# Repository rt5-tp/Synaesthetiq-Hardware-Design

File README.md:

# SynaesthetiQ Hardware

SynaesthetiQ's hardware centre's around a pair of flexible LED Matrices which have been wrapped around a 3D printed core, palced on top of this core is a 30W RGB COB LED.

## AuxBoard

SynaesthetiQ has an Auxillary Board which provides power to both of the matrices, the big led, Raspberry Pi 4B and a fan for cooling. This board is detailed in the [AuxBoard KiCAD project](./AuxBoard/). This board distributes power provided by an ATX power supply while also providing Back Powering protection from the RPI and polyfuse protection to each of the four areas of supply on the board. AuxBoard provides levelshifting from the 3.3v of the RPI's logic to the 5v of the matrices and the big LED.

### Schematic

### PCB Layout

### Final PCB's
The most recent PCB for the project.

Below is two of the eventual three PCBs made for the project.

## PMOS Switch

Exists to test the functionality of the PMOS Switch circuit being used.

## ZVD Sim

Is a KiCAD project which simulates the Back powering protection built into the SynaesthetiQ AuxBoard.

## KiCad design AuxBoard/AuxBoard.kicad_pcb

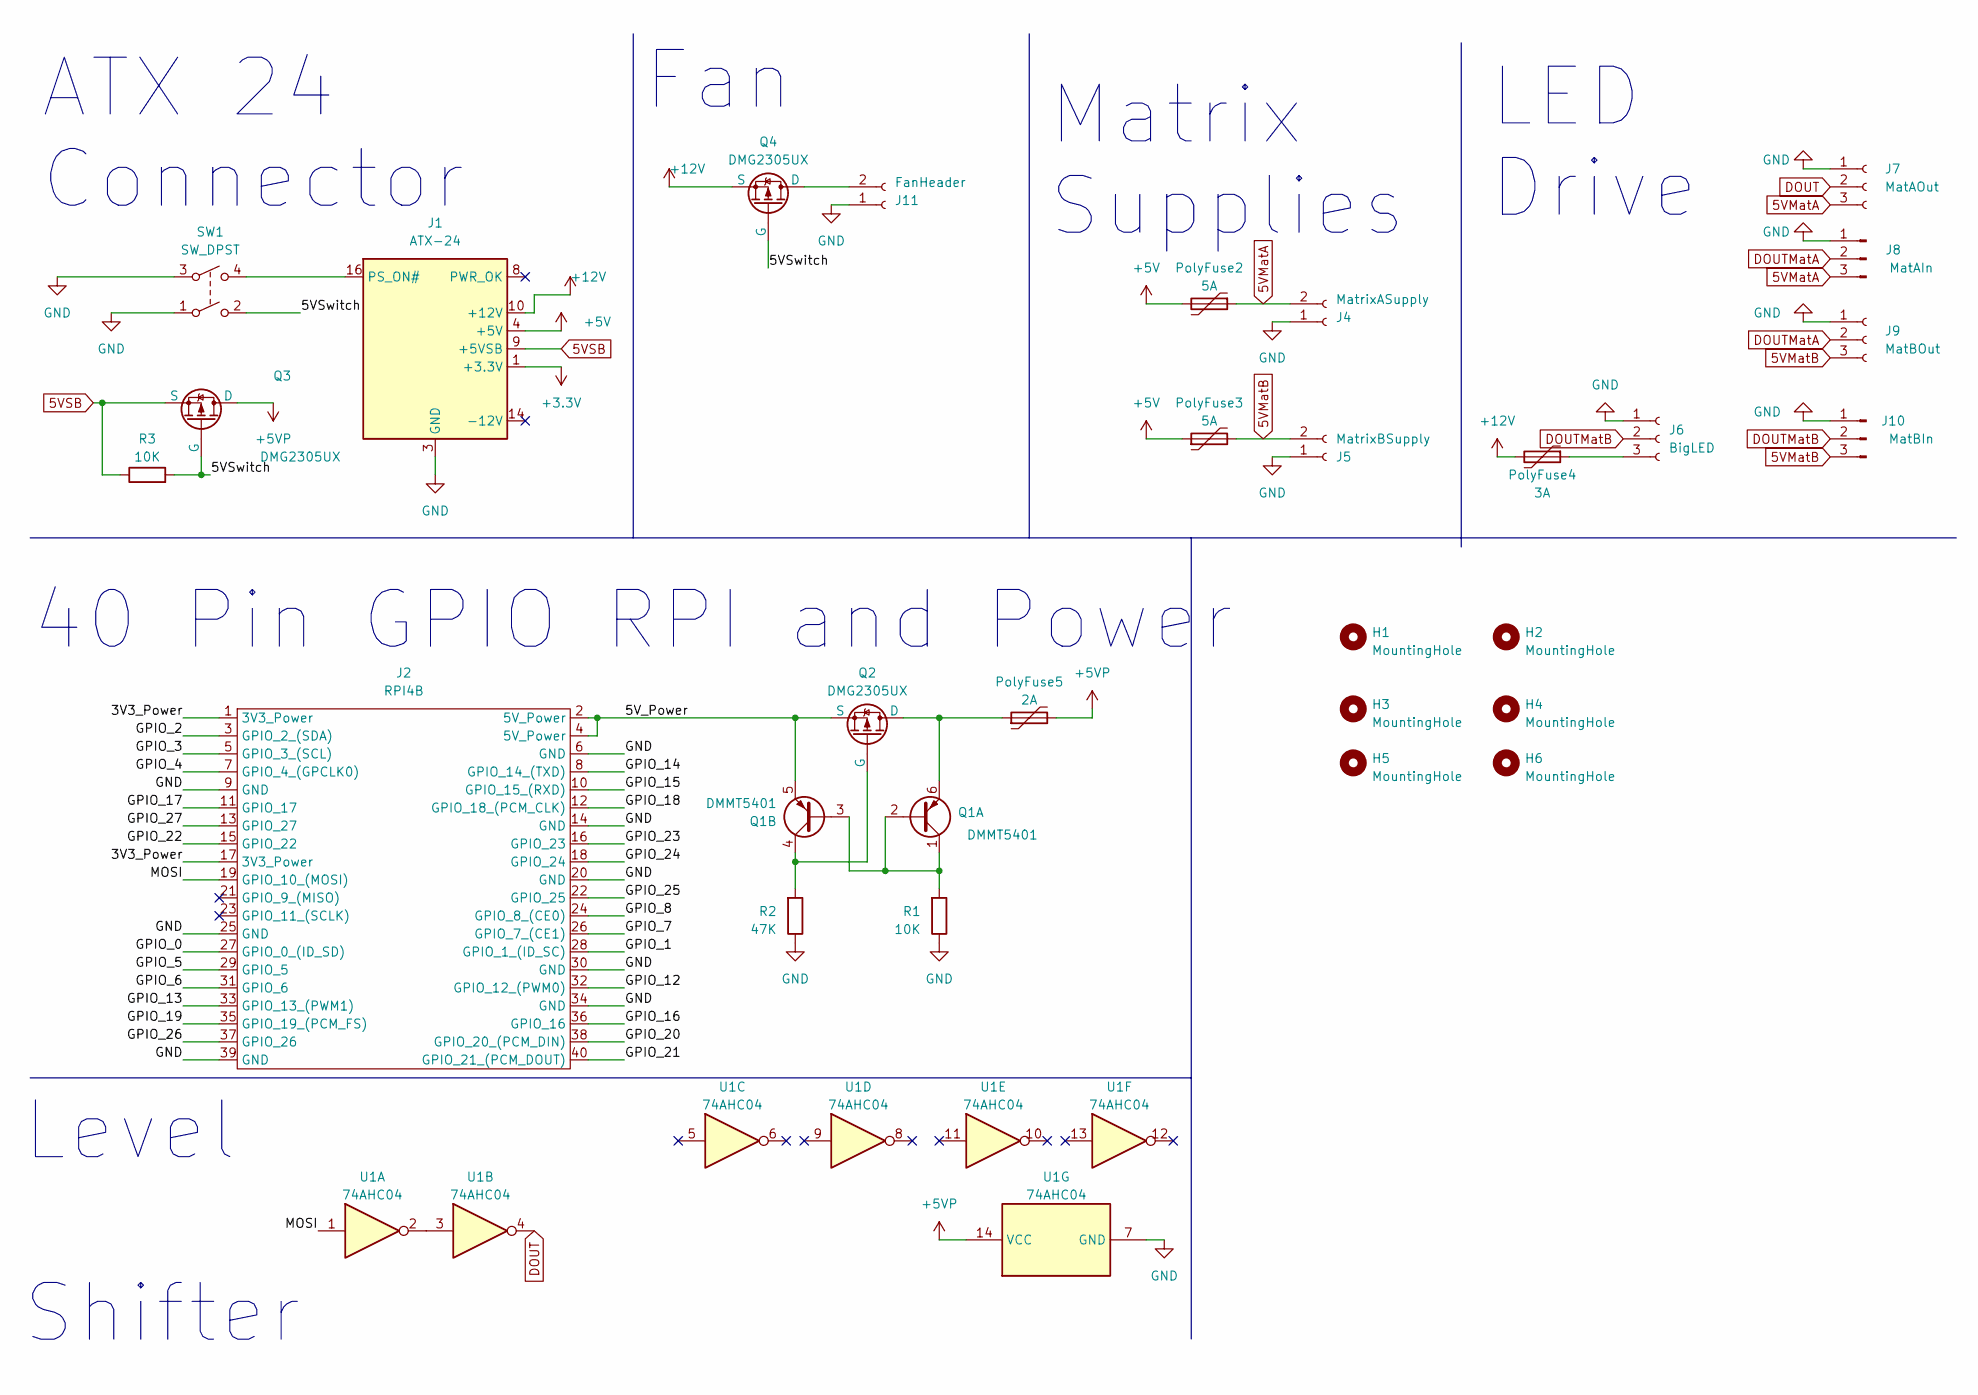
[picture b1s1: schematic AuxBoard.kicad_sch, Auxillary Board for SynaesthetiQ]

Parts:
H1, H2, H3, H4, H5, H6: MountingHole; MountingHole_2.75mm_RPI_HAT
J1: ATX-24; Molex_Mini-Fit_Jr_5569-24A2_2x12_P4.20mm_Horizontal
J2: RPI4B; PI Header Passthrough
J4: MatrixASupply; PinSocket_1x02_P2.54mm_Vertical
J5: MatrixBSupply; PinSocket_1x02_P2.54mm_Vertical
J6: BigLED; PinSocket_1x03_P2.54mm_Vertical
J7: MatAOut; PinSocket_1x03_P2.54mm_Vertical
J8: MatAIn; PinSocket_1x03_P2.54mm_Vertical
J9: MatBOut; PinSocket_1x03_P2.54mm_Vertical
J10: MatBIn; PinSocket_1x03_P2.54mm_Vertical
J11: FanHeader; PinSocket_1x02_P2.54mm_Vertical
PolyFuse2, PolyFuse3: 5A; Fuse_2920_7451Metric_Pad2.10x5.45mm_HandSolder
PolyFuse4: 3A; Fuse_2920_7451Metric_Pad2.10x5.45mm_HandSolder
PolyFuse5: 2A; Fuse_1812_4532Metric_Pad1.30x3.40mm_HandSolder
Q1: DMMT5401; SOT-23-6
Q2, Q3, Q4: DMG2305UX; SOT-23-3
R1, R3: 10K; R_0805_2012Metric_Pad1.20x1.40mm_HandSolder
R2: 47K; R_0805_2012Metric_Pad1.20x1.40mm_HandSolder
SW1: SW_DPST; PinHeader_2x02_P2.54mm_Vertical
U1: 74AHC04; DIP-14_W7.62mm

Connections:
5VMatA: J4.2, J7.3, J8.3, PolyFuse2.1
5VMatB: J5.2, J9.3, J10.3, PolyFuse3.2
5VSB: J1.9 (+5VSB), Q3.2 (S), R3.1
+3.3V: J1.1 (+3.3V), J1.2 (+3.3V), J1.12 (+3.3V), J1.13 (+3.3V)
+5V: J1.4 (+5V), J1.6 (+5V), J1.21 (+5V), J1.22 (+5V), J1.23 (+5V), PolyFuse2.2, PolyFuse3.1
+5VP: PolyFuse5.2, Q3.3 (D), U1.14 (VCC)
+12V: J1.10 (+12V), J1.11 (+12V), PolyFuse4.2, Q4.2 (S)
/3V3_Power: J2.1 (3V3_Power), J2.17 (3V3_Power)
/5VSwitch: Q3.1 (G), Q4.1 (G), R3.2, SW1.2
/5V_Power: J2.2 (5V_Power), J2.4 (5V_Power), Q1.5 (E2), Q2.2 (S)
/GPIO_0: J2.27 (GPIO_0_(ID_SD))
/GPIO_1: J2.28 (GPIO_1_(ID_SC))
/GPIO_2: J2.3 (GPIO_2_(SDA))
/GPIO_3: J2.5 (GPIO_3_(SCL))
/GPIO_4: J2.7 (GPIO_4_(GPCLK0))
/GPIO_5: J2.29 (GPIO_5)
/GPIO_6: J2.31 (GPIO_6)
/GPIO_7: J2.26 (GPIO_7_(CE1))
/GPIO_8: J2.24 (GPIO_8_(CE0))
/GPIO_12: J2.32 (GPIO_12_(PWM0))
/GPIO_13: J2.33 (GPIO_13_(PWM1))
/GPIO_14: J2.8 (GPIO_14_(TXD))
/GPIO_15: J2.10 (GPIO_15_(RXD))
/GPIO_16: J2.36 (GPIO_16)
/GPIO_17: J2.11 (GPIO_17)
/GPIO_18: J2.12 (GPIO_18_(PCM_CLK))
/GPIO_19: J2.35 (GPIO_19_(PCM_FS))
/GPIO_20: J2.38 (GPIO_20_(PCM_DIN))
/GPIO_21: J2.40 (GPIO_21_(PCM_DOUT))
/GPIO_22: J2.15 (GPIO_22)
/GPIO_23: J2.16 (GPIO_23)
/GPIO_24: J2.18 (GPIO_24)
/GPIO_25: J2.22 (GPIO_25)
/GPIO_26: J2.37 (GPIO_26)
/GPIO_27: J2.13 (GPIO_27)
/MOSI: J2.19 (GPIO_10_(MOSI)), U1.1
DOUT: J7.2, U1.4
DOUTMatA: J8.2, J9.2
DOUTMatB: J6.2, J10.2
GND: J1.3 (GND), J1.5 (GND), J1.7 (GND), J1.15 (GND), J1.17 (GND), J1.18 (GND), J1.19 (GND), J1.24 (GND), J2.6 (GND), J2.9 (GND), J2.14 (GND), J2.20 (GND), J2.25 (GND), J2.30 (GND), J2.34 (GND), J2.39 (GND), J4.1, J5.1, J6.1, J7.1, J8.1, J9.1, J10.1, J11.1, R1.1, R2.1, SW1.1, SW1.3, U1.7 (GND)
unnamed: J1.16 (PS_ON#), SW1.4
unnamed: J6.3, PolyFuse4.1
unnamed: J11.2, Q4.3 (D)
unnamed: Q1.1 (C1), Q1.2 (B1), Q1.3 (B2), R1.2
unnamed: PolyFuse5.1, Q1.6 (E1), Q2.3 (D)
unnamed: Q1.4 (C2), Q2.1 (G), R2.2
unnamed: U1.2, U1.3

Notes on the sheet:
ATX 24 Connector
Fan
Level Shifter
LED Drive
40 Pin GPIO RPI and Power
Matrix Supplies

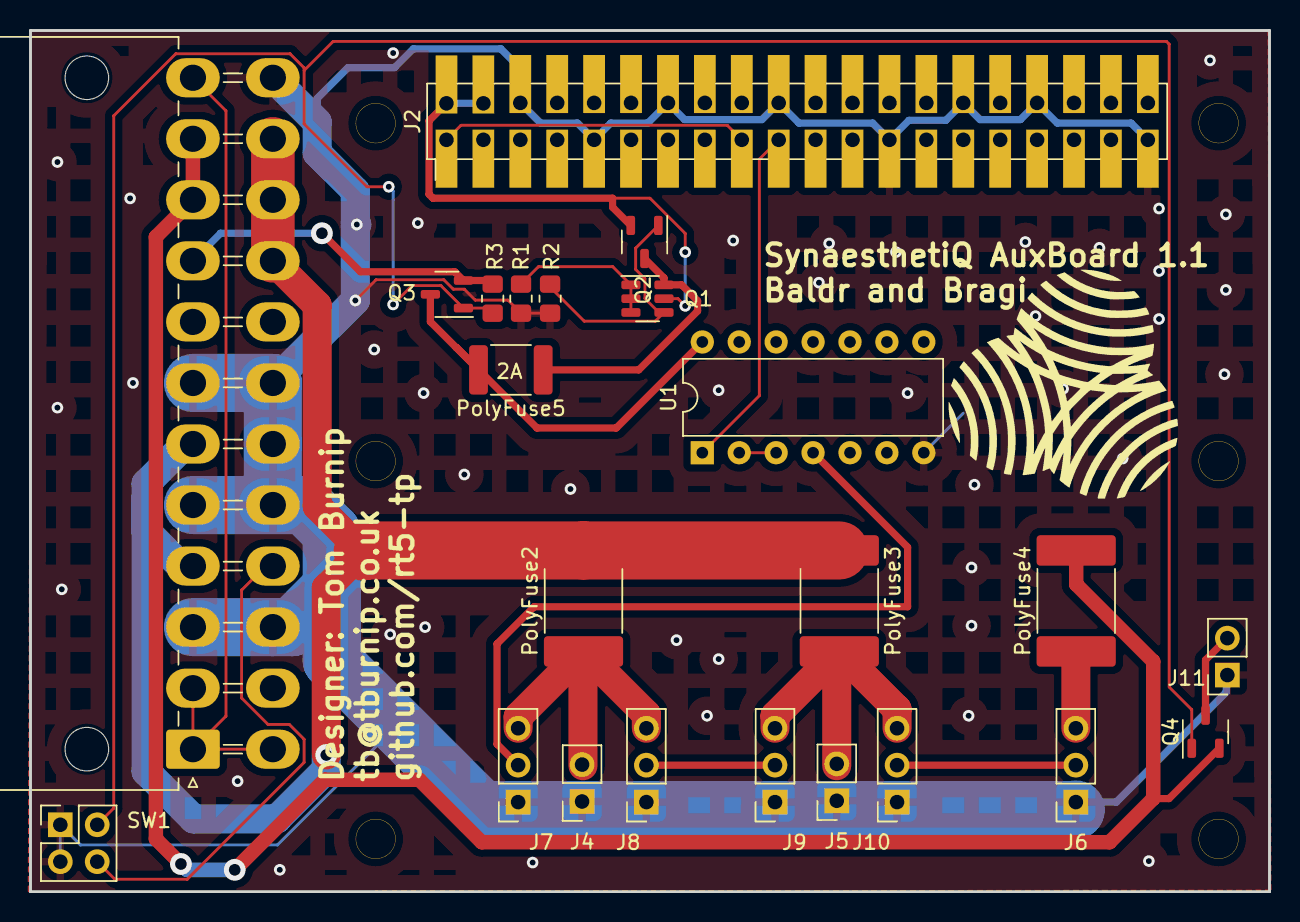
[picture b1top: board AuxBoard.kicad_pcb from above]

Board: 2 copper layers, 85.2 x 59.2 mm, 29 parts (0 on the bottom side), 22 nets.

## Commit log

2023-02-18 Intial Daughter Board Design
2023-02-18 Added headers to handle comms with Matrices and Big LED
2023-02-22 Power Distro Changes
2023-02-24 Adding Basic CI for kicad
2023-02-24 Changes to ci
2023-02-24 Fixes once again
2023-02-24 Test
2023-02-24 Fixed command
2023-02-26 Added seccond GPIO
2023-02-26 Draft Schematic Finished. Added ZVD and Changed to polyfuses
2023-02-27 Added fan header and mosfet control for PI power supply
2023-03-06 Simulated Ideal Diode to check functionality. Swaped Tristate buffer for hex inverter. Swapped to passthrough footprint.
2023-03-06 Final PCB Layout
2023-03-06 Filled GND Net. Fixed most 3d elements
2023-03-06 Added Silkscreen
2023-03-07 Gerbers for PCB. Fixed RPI Header Mistake. PCB will need bodge.
2023-03-22 Fixing Header Orientation
2023-04-01 Updates to the Aux Board PCB
2023-04-17 Current AuxBoard and README
2023-04-17 Improving the readme
2023-04-17 Added info on other KiCAD Projects
2023-04-17 Adding More Images of Hardware
2023-04-17 Added a picture of the most recent PCB to the readme.
